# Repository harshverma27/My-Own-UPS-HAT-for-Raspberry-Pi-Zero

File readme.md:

# 🔋 Raspberry Pi Zero 2 UPS (TP4056 + DW01A + TPS61236)

## 📌 Overview

This project is a **budget-friendly UPS (Uninterruptible Power Supply)** designed specifically for the **Raspberry Pi Zero 2**.

I built this because I personally use a **Pi Zero 2**, and I needed a **reliable battery backup (UPS)** for it.
Most ready-made UPS solutions available are either:

* Too expensive
* Overkill for Pi Zero
* Poorly designed or unreliable

So instead of buying one, **I designed my own UPS PCB from scratch**.

This design uses **commonly available and low-cost ICs** while still following **proper battery safety and power design practices**.

---

## 🧩 Project Architecture

The PCB is divided into **three main functional blocks**:

1. **Battery Protection Circuit**
2. **Battery Charging Circuit**
3. **Boost Converter (5V Output for Raspberry Pi)**

Each block is electrically separated but works together as a complete system.

---

## 🔋 1. Battery Protection (DW01A + MOSFETs)

Lithium-ion batteries must **never** be:

* Over-discharged
* Over-charged
* Short-circuited

To ensure safety, this design uses the **DW01A battery protection IC** along with external MOSFETs.

### What this block does:

* Cuts off the load if battery voltage drops too low (low-voltage cutoff)
* Protects against over-current and short-circuit
* Protects the battery during charging and discharging

This ensures the 18650 cell is always operating within safe limits.

---

## 🔌 2. Battery Charging Circuit (TP4056)

Charging is handled by the **TP4056**, a popular and reliable **single-cell Li-ion charger IC**.

### Why TP4056:

* Simple linear charger
* Constant Current / Constant Voltage (CC/CV) charging
* Reliable and widely used
* Easy to configure charging current

### Important design choice:

The **TP4056 is used only for charging**.
It does **not power the load directly**.

The battery is always protected by the **DW01A**, and the charger connects safely through the protection circuit.

---

## ⚡ 3. Boost Converter (TPS61236)

The Raspberry Pi Zero 2 requires a **stable 5V supply**.

Since a single 18650 battery provides **3.0V–4.2V**, a boost converter is required.

This project uses the **TPS61236** boost converter.

### What this block does:

* Boosts battery voltage to a stable **5V**
* Provides enough current for Raspberry Pi Zero 2
* Designed with proper layout considerations for efficiency and stability

The boost converter draws power **only through the protected battery path**, ensuring the battery is never over-discharged.

---

## 🔁 How Everything Works Together

1. **Battery powers the system** through the protection circuit
2. **Boost converter generates 5V** for Raspberry Pi Zero 2
3. **TP4056 charges the battery** when external power is available
4. If external power is removed:

   * Battery instantly takes over
   * Pi continues running without reboot
5. If battery voltage becomes too low:

   * DW01A disconnects the load to protect the battery

This makes the system act like a **true UPS**.

---

## 🎯 Why I Built This Project

* I own a **Raspberry Pi Zero 2**
* I needed a **low-cost, reliable UPS**
* Commercial solutions were expensive or poorly suited
* I wanted:

  * Battery safety
  * Proper power design
  * Full control over the hardware
* This project was also a **learning experience in power electronics and PCB design**

---

## 🛠️ Features

* Li-ion battery support (3.7V)
* Battery protection (LVC, OCP, SCP)
* Safe and reliable charging
* 5V regulated output for Raspberry Pi Zero 2
* Budget-friendly and open-source
* Designed as a **PCB**, not a breadboard hack

---

## 📂 Repository Contents

* `Kicad Projtect/` – Full Kicad Projtect
* `gerbers/` – Manufacturing-ready files
* `README.md` – Project documentation

---

## ⚠️ Disclaimer

This project involves **lithium-ion batteries**.
Improper handling or incorrect assembly can cause damage or injury.

Build and use at your own risk.
Always verify connections before inserting a battery.

---

## ⭐ Future Improvements

* Battery percentage monitoring
* Load current measurement
* Power-fail detection GPIO for Raspberry Pi
* Multiple-cell support

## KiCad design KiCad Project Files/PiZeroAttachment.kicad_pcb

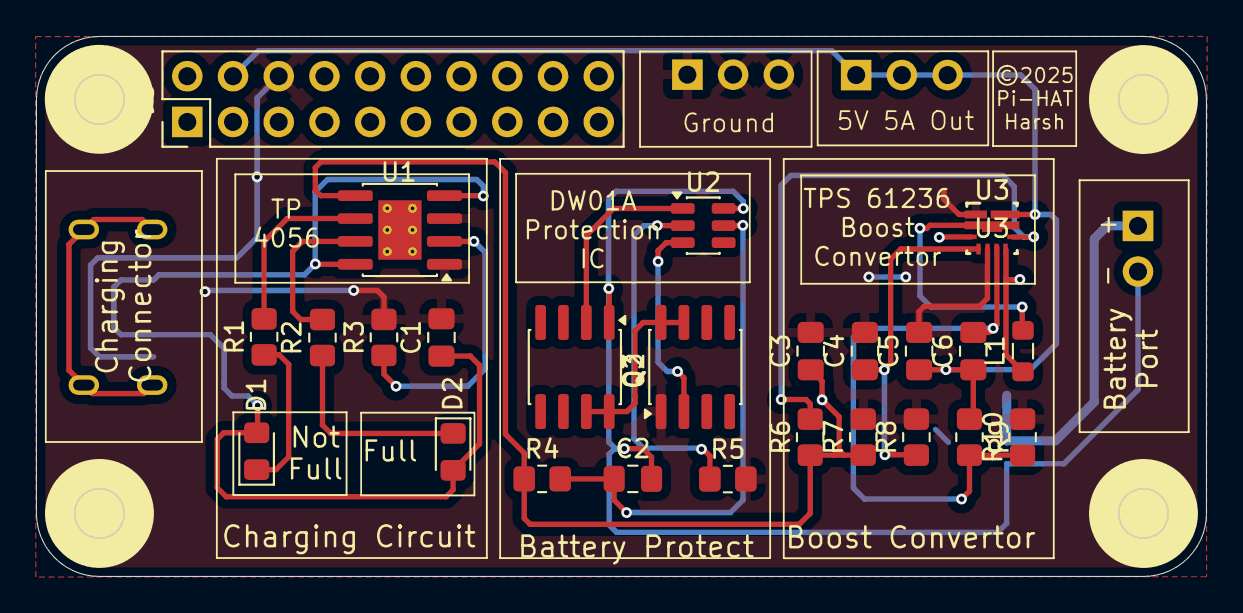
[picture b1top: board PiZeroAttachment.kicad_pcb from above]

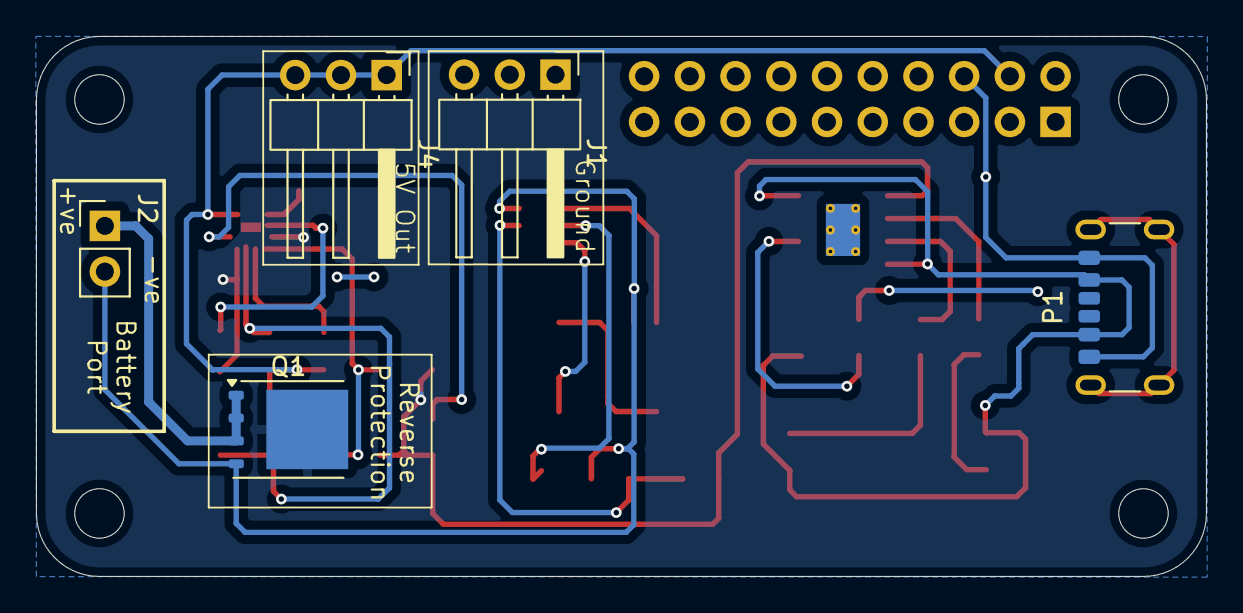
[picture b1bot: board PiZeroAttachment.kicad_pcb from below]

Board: 2 copper layers, 65.0 x 30.0 mm, 30 parts (5 on the bottom side), 20 nets.

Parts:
C1: 10uF; C_0805_2012Metric_Pad1.18x1.45mm_HandSolder
C2: 0.1uF; C_0805_2012Metric_Pad1.18x1.45mm_HandSolder
C3: 10uF 5.787mOhm; C_0805_2012Metric_Pad1.18x1.45mm_HandSolder
C4: 10nF 1mOhm; C_0805_2012Metric_Pad1.18x1.45mm_HandSolder
C5: 47uF; C_0805_2012Metric_Pad1.18x1.45mm_HandSolder
C6: 10pF; C_0805_2012Metric_Pad1.18x1.45mm_HandSolder
D1: LED (RED); LED_0805_2012Metric_Pad1.15x1.40mm_HandSolder
D2: LED (GREEN); LED_0805_2012Metric_Pad1.15x1.40mm_HandSolder
J1, J4: Conn_01x03_Pin; PinHeader_1x03_P2.54mm_Horizontal
J2: Conn_01x02_Pin; PinHeader_1x02_P2.54mm_Vertical
J5: Conn_02x10_Odd_Even; PinHeader_2x10_P2.54mm_Vertical
L1: 1uH 10mOhm; L_0805_2012Metric_Pad1.05x1.20mm_HandSolder
P1: USB_C_Plug_USB2.0; USB_C_Receptacle_GCT_USB4125-xx-x_6P_TopMnt_Horizontal
Q1: FDMS86350; TDSON-8-1
Q2, Q3: AO4842; SOIC-8_3.9x4.9mm_P1.27mm
R1, R2: 1k; R_0805_2012Metric_Pad1.20x1.40mm_HandSolder
R3: 2k; R_0805_2012Metric_Pad1.20x1.40mm_HandSolder
R4: 100 ohm; R_0805_2012Metric_Pad1.20x1.40mm_HandSolder
R5: 1k ohm; R_0805_2012Metric_Pad1.20x1.40mm_HandSolder
R6, R7: 1M Ohm; R_0805_2012Metric_Pad1.20x1.40mm_HandSolder
R8: 30.9k Ohm; R_0805_2012Metric_Pad1.20x1.40mm_HandSolder
R9: 619k Ohm; R_0805_2012Metric_Pad1.20x1.40mm_HandSolder
R10: 205k Ohm; R_0805_2012Metric_Pad1.20x1.40mm_HandSolder
U1: TP4056-42-ESOP8; SOIC-8-1EP_3.9x4.9mm_P1.27mm_EP2.41x3.3mm_ThermalVias
U2: DW01A; SOT-23-6
U3: TPS61236PRWLR; RWL0009A

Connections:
5V+: C5.1, C6.1, J4.1, J4.2, J4.3, J5.4, R9.1, U3.9 (VOUT)
5V-: C1.2, C3.2, C4.2, C5.2, J1.1, J1.2, J1.3, J5.6, P1.A12 (GND), P1.B12 (GND), Q3.1 (S1), R3.2, R5.2, R7.2, R8.2, R10.2, U1.1 (TEMP), U1.3 (GND), U3.1 (PGND), U3.5 (AGND)
BAT+: C3.1, L1.1, Q1.5 (D), R4.1, R6.1, R7.1, U1.5 (BAT), U3.3 (VIN), U3.7 (EN)
BAT-: C2.2, J2.2, Q1.4 (G), Q2.1 (S1), U2.6 (GND)
unnamed: C1.1, D1.2 (A), D2.2 (A), P1.A9 (VBUS), P1.B9 (VBUS), U1.4 (V_{CC}), U1.8 (CE)
unnamed: D1.1 (K), R1.1
unnamed: D2.1 (K), R2.1
unnamed: J2.1, Q1.1 (S), Q1.2 (S), Q1.3 (S)
unnamed: Q2.7 (D1), Q2.8 (D1), Q3.7 (D1), Q3.8 (D1)
unnamed: Q2.2 (G1), U2.1 (OD)
unnamed: Q3.2 (G1), U2.3 (OC)
unnamed: R3.1, U1.2 (PROG)
unnamed: R2.2, U1.7 (~CHRG)
unnamed: R1.2, U1.6 (~STDBY)
unnamed: R5.1, U2.2 (CS)
unnamed: C2.1, R4.2, U2.5 (VCC)
unnamed: C4.1, R8.1, U3.4 (CC)
unnamed: C6.2, R9.2, R10.1, U3.6 (FB)
unnamed: R6.2, U3.8 (INACT)
unnamed: L1.2, U3.2 (SW)

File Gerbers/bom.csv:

Designator,Footprint,Quantity,Value,LCSC Part #
C1,0805,1,10uF,
C2,0805,1,0.1uF,
C3,0805,1,10uF 5.787mOhm,
C4,0805,1,10nF 1mOhm,
C5,0805,1,47uF,
C6,0805,1,10pF,
D1,0805,1,LED (RED),
D2,0805,1,LED (GREEN),
"J1, J4",PinHeader_1x03_P2.54mm_Horizontal,2,Conn_01x03_Pin,
J2,PinHeader_1x02_P2.54mm_Vertical,1,Conn_01x02_Pin,
J5,PinHeader_2x10_P2.54mm_Vertical,1,Conn_02x10_Odd_Even,
L1,0805,1,1uH 10mOhm,
P1,USB_C_Receptacle_GCT_USB4125-xx-x_6P_TopMnt_Horizontal,1,USB_C_Plug_USB2.0,
Q1,TDSON-8-1,1,FDMS86350,
"Q2, Q3",SOIC-8_3.9x4.9mm_P1.27mm,2,AO4842,
"R1, R2",0805,2,1k,
R10,0805,1,205k Ohm,
R3,0805,1,2k,
R4,0805,1,100 ohm,
R5,0805,1,1k ohm,
"R6, R7",0805,2,1M Ohm,
R8,0805,1,30.9k Ohm,
R9,0805,1,619k Ohm,
U1,SOIC-8-1EP_3.9x4.9mm_P1.27mm_EP2.41x3.3mm_ThermalVias,1,TP4056-42-ESOP8,
U2,SOT-23-6,1,DW01A,
U3,RWL0009A,1,TPS61236PRWLR,

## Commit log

2025-12-15 Initial Commit
    Commiting everything at once, because I forgot to create a repository.
2025-12-15 Main Commit
    I forgot to create a repo so here's everything at once
2025-12-15 Add Images

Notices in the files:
KiCad Project Files/PiZeroAttachment.kicad_pcb:
©2025
